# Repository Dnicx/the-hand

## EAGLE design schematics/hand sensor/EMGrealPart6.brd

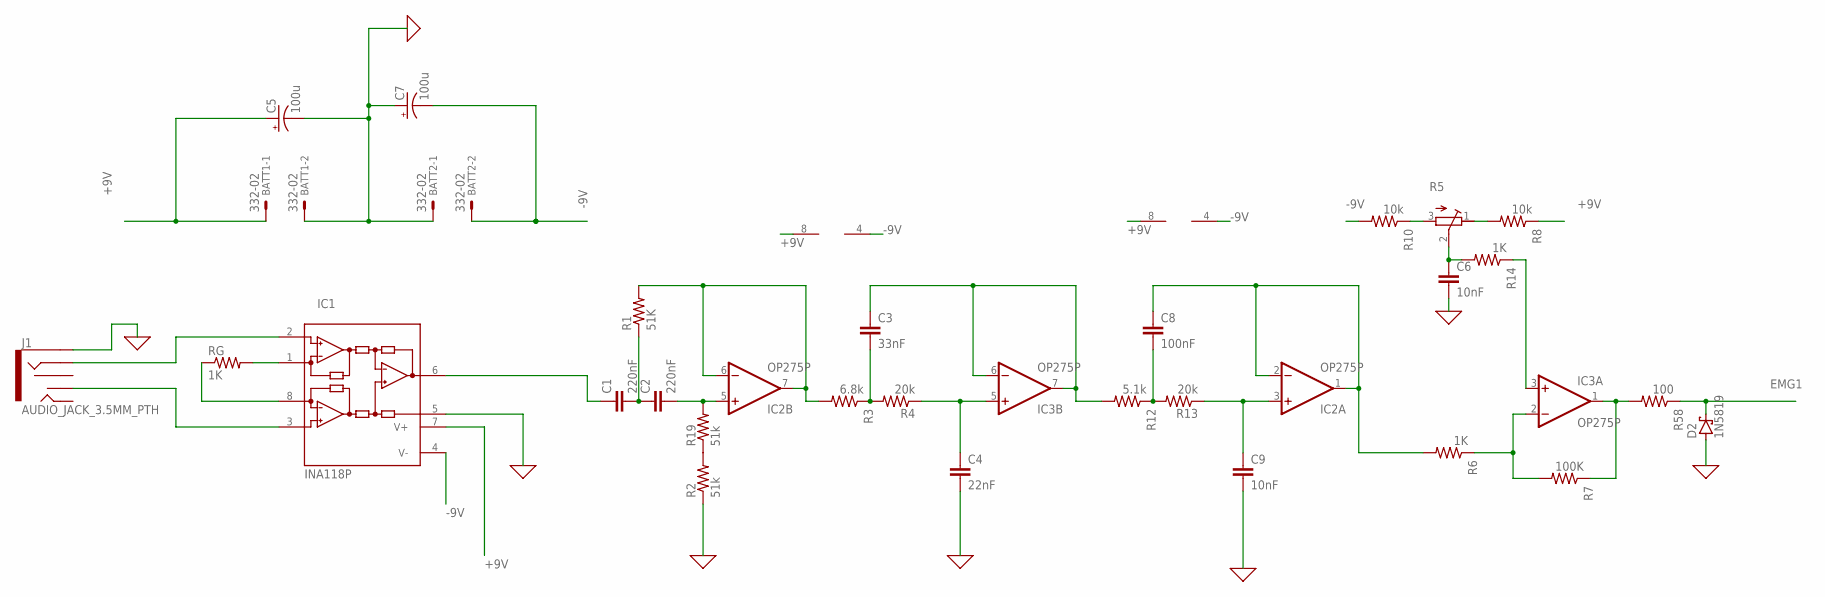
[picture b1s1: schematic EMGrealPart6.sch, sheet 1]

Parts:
BATT1, BATT2: 332-02
C1, C2: 220nF; C050-025X075
C3: 33nF; C050-025X075
C4: 22nF; C050-025X075
C5, C7: 100u; E2,5-6
C6, C9: 10nF; C050-025X075
C8: 100nF; C050-025X075
D2: 1N5819; F126Z12
IC1: INA118P; DIL08
IC2, IC3: OP275P; DIL08
J1: AUDIO_JACK_3.5MM_PTH; AUDIO-JACK
R1: 51K; 0207/12
R2, R19: 51k; 0207/12
R3: 6.8k; 0207/12
R4, R13: 20k; 0207/12
R5: R-TRIMMT93YA; RTRIMT93YA
R6, R14: 1K; 0207/12
R7: 100K; 0207/12
R8, R10: 10k; 0207/12
R12: 5.1k; 0207/12
R58: 100; 0207/12
RG: 1K; 0207/12

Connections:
0: BATT1.2, BATT2.1, C4.2, C5.-, C6.2, C7.+, C9.2, D2.A, IC1.5 (REF), J1.SLEEVE, R2.1; also elsewhere on the board
+9V: BATT1.1, C5.+, IC1.7 (V+), IC2.8 (V+), IC3.8 (V+), R8.1; also elsewhere on the board
-9V: BATT2.2, C7.-, IC1.4 (V-), IC2.4 (V-), IC3.4 (V-), R10.2; also elsewhere on the board
EMG1: D2.C, R58.1; also elsewhere on the board
unnamed: IC1.1 (RG), RG.2
unnamed: IC1.8 (RG), RG.1
unnamed: IC1.2 (-IN), J1.RING
unnamed: C8.2, R12.1, R13.2
unnamed: C1.2, C2.1, R1.1
unnamed: C1.1, IC1.6 (OUT)
unnamed: C2.2, IC2.5 (+IN), R19.2
unnamed: IC2.6 (-IN), IC2.7 (OUT), R1.2, R3.2
unnamed: C3.2, R3.1, R4.2
unnamed: C4.1, IC3.5 (+IN), R4.1
unnamed: C3.1, IC3.6 (-IN), IC3.7 (OUT), R12.2
unnamed: C9.1, IC2.3 (+IN), R13.1
unnamed: R5.3 (A), R10.1
unnamed: C6.1, R5.2 (S), R14.2
unnamed: IC3.2 (-IN), R6.1, R7.2
unnamed: R2.2, R19.1
unnamed: C8.1, IC2.1 (OUT), IC2.2 (-IN), R6.2
unnamed: R5.1 (E), R8.2
unnamed: IC3.3 (+IN), R14.1
unnamed: IC1.3 (+IN), J1.TSH
unnamed: IC3.1 (OUT), R7.1, R58.2

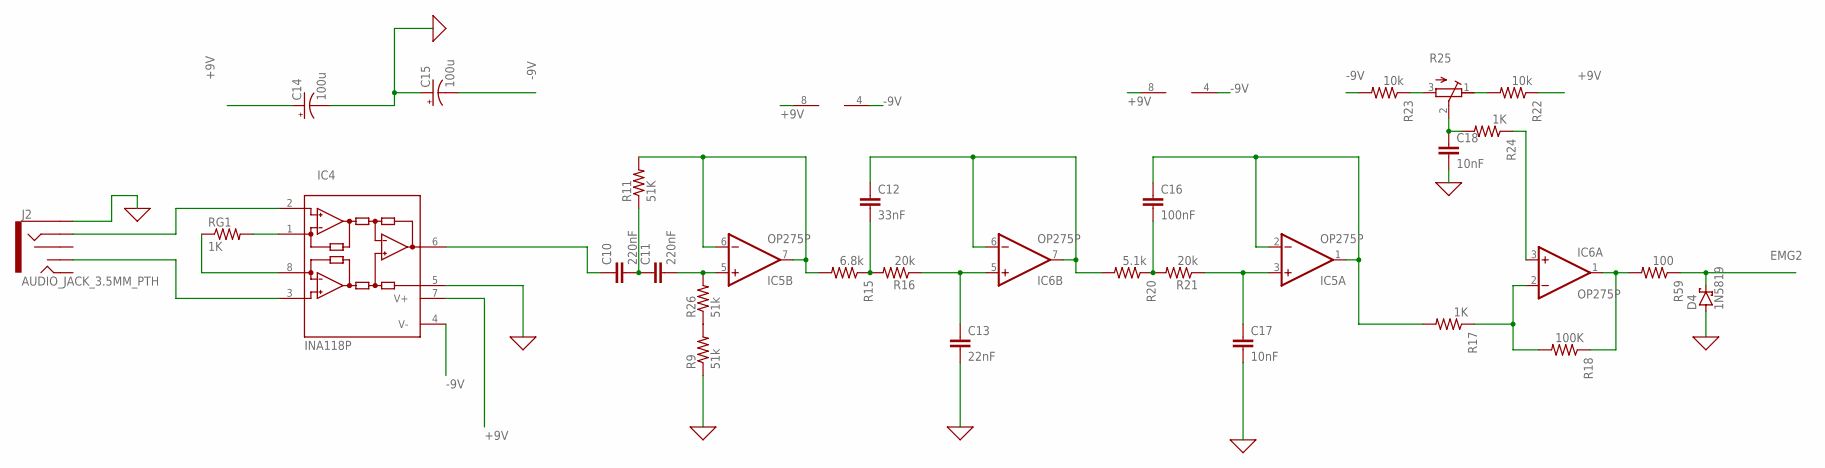
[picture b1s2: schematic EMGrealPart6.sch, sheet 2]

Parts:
C10, C11: 220nF; C050-025X075
C12: 33nF; C050-025X075
C13: 22nF; C050-025X075
C14, C15: 100u; E2,5-6
C16: 100nF; C050-025X075
C17, C18: 10nF; C050-025X075
D4: 1N5819; F126Z12
IC4: INA118P; DIL08
IC5, IC6: OP275P; DIL08
J2: AUDIO_JACK_3.5MM_PTH; AUDIO-JACK
R9, R26: 51k; 0207/12
R11: 51K; 0207/12
R15: 6.8k; 0207/12
R16, R21: 20k; 0207/12
R17, R24: 1K; 0207/12
R18: 100K; 0207/12
R20: 5.1k; 0207/12
R22, R23: 10k; 0207/12
R25: R-TRIMMT93YA; RTRIMT93YA
R59: 100; 0207/12
RG1: 1K; 0207/12

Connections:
0: C13.2, C14.-, C15.+, C17.2, C18.2, D4.A, IC4.5 (REF), J2.SLEEVE, R9.1; also elsewhere on the board
+9V: C14.+, IC4.7 (V+), IC5.8 (V+), IC6.8 (V+), R22.1; also elsewhere on the board
-9V: C15.-, IC4.4 (V-), IC5.4 (V-), IC6.4 (V-), R23.2; also elsewhere on the board
EMG2: D4.C, R59.1; also elsewhere on the board
unnamed: IC4.1 (RG), RG1.2
unnamed: IC4.8 (RG), RG1.1
unnamed: C10.1, IC4.6 (OUT)
unnamed: C10.2, C11.1, R11.1
unnamed: C11.2, IC5.5 (+IN), R26.2
unnamed: IC5.6 (-IN), IC5.7 (OUT), R11.2, R15.2
unnamed: C12.2, R15.1, R16.2
unnamed: C13.1, IC6.5 (+IN), R16.1
unnamed: C12.1, IC6.6 (-IN), IC6.7 (OUT), R20.2
unnamed: IC6.2 (-IN), R17.1, R18.2
unnamed: IC6.1 (OUT), R18.1, R59.2
unnamed: C16.2, R20.1, R21.2
unnamed: C17.1, IC5.3 (+IN), R21.1
unnamed: IC4.2 (-IN), J2.RING
unnamed: C16.1, IC5.1 (OUT), IC5.2 (-IN), R17.2
unnamed: IC4.3 (+IN), J2.TSH
unnamed: R23.1, R25.3 (A)
unnamed: R22.2, R25.1 (E)
unnamed: IC6.3 (+IN), R24.1
unnamed: C18.1, R24.2, R25.2 (S)
unnamed: R9.2, R26.1

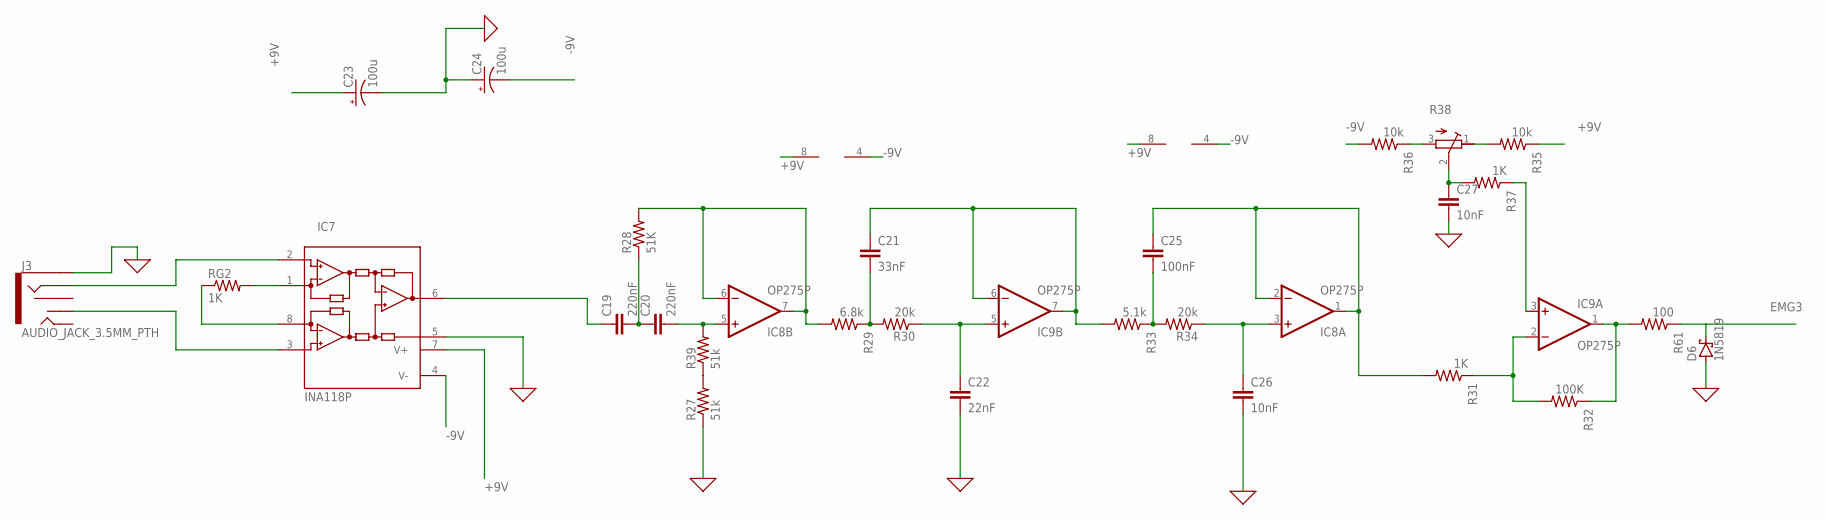
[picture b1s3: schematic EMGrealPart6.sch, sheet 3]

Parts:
C19, C20: 220nF; C050-025X075
C21: 33nF; C050-025X075
C22: 22nF; C050-025X075
C23, C24: 100u; E2,5-6
C25: 100nF; C050-025X075
C26, C27: 10nF; C050-025X075
D6: 1N5819; F126Z12
IC7: INA118P; DIL08
IC8, IC9: OP275P; DIL08
J3: AUDIO_JACK_3.5MM_PTH; AUDIO-JACK
R27, R39: 51k; 0207/12
R28: 51K; 0207/12
R29: 6.8k; 0207/12
R30, R34: 20k; 0207/12
R31, R37: 1K; 0207/12
R32: 100K; 0207/12
R33: 5.1k; 0207/12
R35, R36: 10k; 0207/12
R38: R-TRIMMT93YA; RTRIMT93YA
R61: 100; 0207/12
RG2: 1K; 0207/12

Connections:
0: C22.2, C23.-, C24.+, C26.2, C27.2, D6.A, IC7.5 (REF), J3.SLEEVE, R27.1; also elsewhere on the board
+9V: C23.+, IC7.7 (V+), IC8.8 (V+), IC9.8 (V+), R35.1; also elsewhere on the board
-9V: C24.-, IC7.4 (V-), IC8.4 (V-), IC9.4 (V-), R36.2; also elsewhere on the board
EMG3: D6.C, R61.1; also elsewhere on the board
unnamed: IC7.1 (RG), RG2.2
unnamed: IC7.8 (RG), RG2.1
unnamed: C19.1, IC7.6 (OUT)
unnamed: C19.2, C20.1, R28.1
unnamed: C20.2, IC8.5 (+IN), R39.2
unnamed: IC8.6 (-IN), IC8.7 (OUT), R28.2, R29.2
unnamed: C21.2, R29.1, R30.2
unnamed: C22.1, IC9.5 (+IN), R30.1
unnamed: C21.1, IC9.6 (-IN), IC9.7 (OUT), R33.2
unnamed: IC9.2 (-IN), R31.1, R32.2
unnamed: IC9.1 (OUT), R32.1, R61.2
unnamed: C25.2, R33.1, R34.2
unnamed: C26.1, IC8.3 (+IN), R34.1
unnamed: IC7.2 (-IN), J3.RING
unnamed: C25.1, IC8.1 (OUT), IC8.2 (-IN), R31.2
unnamed: IC7.3 (+IN), J3.TSH
unnamed: R36.1, R38.3 (A)
unnamed: R35.2, R38.1 (E)
unnamed: IC9.3 (+IN), R37.1
unnamed: C27.1, R37.2, R38.2 (S)
unnamed: R27.2, R39.1

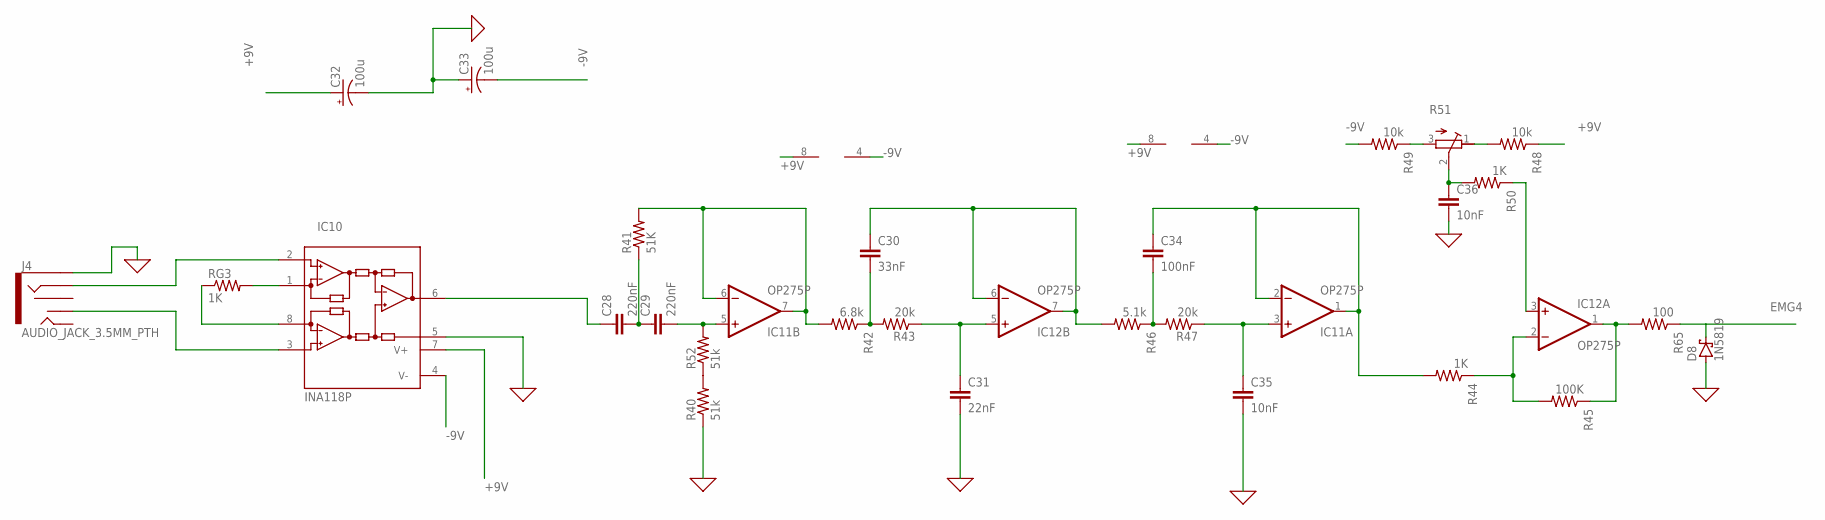
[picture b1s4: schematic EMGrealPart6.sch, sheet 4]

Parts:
C28, C29: 220nF; C050-025X075
C30: 33nF; C050-025X075
C31: 22nF; C050-025X075
C32, C33: 100u; E2,5-6
C34: 100nF; C050-025X075
C35, C36: 10nF; C050-025X075
D8: 1N5819; F126Z12
IC10: INA118P; DIL08
IC11, IC12: OP275P; DIL08
J4: AUDIO_JACK_3.5MM_PTH; AUDIO-JACK
R40, R52: 51k; 0207/12
R41: 51K; 0207/12
R42: 6.8k; 0207/12
R43, R47: 20k; 0207/12
R44, R50: 1K; 0207/12
R45: 100K; 0207/12
R46: 5.1k; 0207/12
R48, R49: 10k; 0207/12
R51: R-TRIMMT93YA; RTRIMT93YA
R65: 100; 0207/12
RG3: 1K; 0207/12

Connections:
0: C31.2, C32.-, C33.+, C35.2, C36.2, D8.A, IC10.5 (REF), J4.SLEEVE, R40.1; also elsewhere on the board
+9V: C32.+, IC10.7 (V+), IC11.8 (V+), IC12.8 (V+), R48.1; also elsewhere on the board
-9V: C33.-, IC10.4 (V-), IC11.4 (V-), IC12.4 (V-), R49.2; also elsewhere on the board
EMG4: D8.C; also elsewhere on the board
unnamed: IC10.1 (RG), RG3.2
unnamed: IC10.8 (RG), RG3.1
unnamed: C28.1, IC10.6 (OUT)
unnamed: C28.2, C29.1, R41.1
unnamed: C29.2, IC11.5 (+IN), R52.2
unnamed: IC11.6 (-IN), IC11.7 (OUT), R41.2, R42.2
unnamed: C30.2, R42.1, R43.2
unnamed: C31.1, IC12.5 (+IN), R43.1
unnamed: C30.1, IC12.6 (-IN), IC12.7 (OUT), R46.2
unnamed: IC12.2 (-IN), R44.1, R45.2
unnamed: IC12.1 (OUT), R45.1, R65.2
unnamed: C34.2, R46.1, R47.2
unnamed: C35.1, IC11.3 (+IN), R47.1
unnamed: IC10.2 (-IN), J4.RING
unnamed: C34.1, IC11.1 (OUT), IC11.2 (-IN), R44.2
unnamed: IC10.3 (+IN), J4.TSH
unnamed: R49.1, R51.3 (A)
unnamed: R48.2, R51.1 (E)
unnamed: IC12.3 (+IN), R50.1
unnamed: C36.1, R50.2, R51.2 (S)
unnamed: R40.2, R52.1

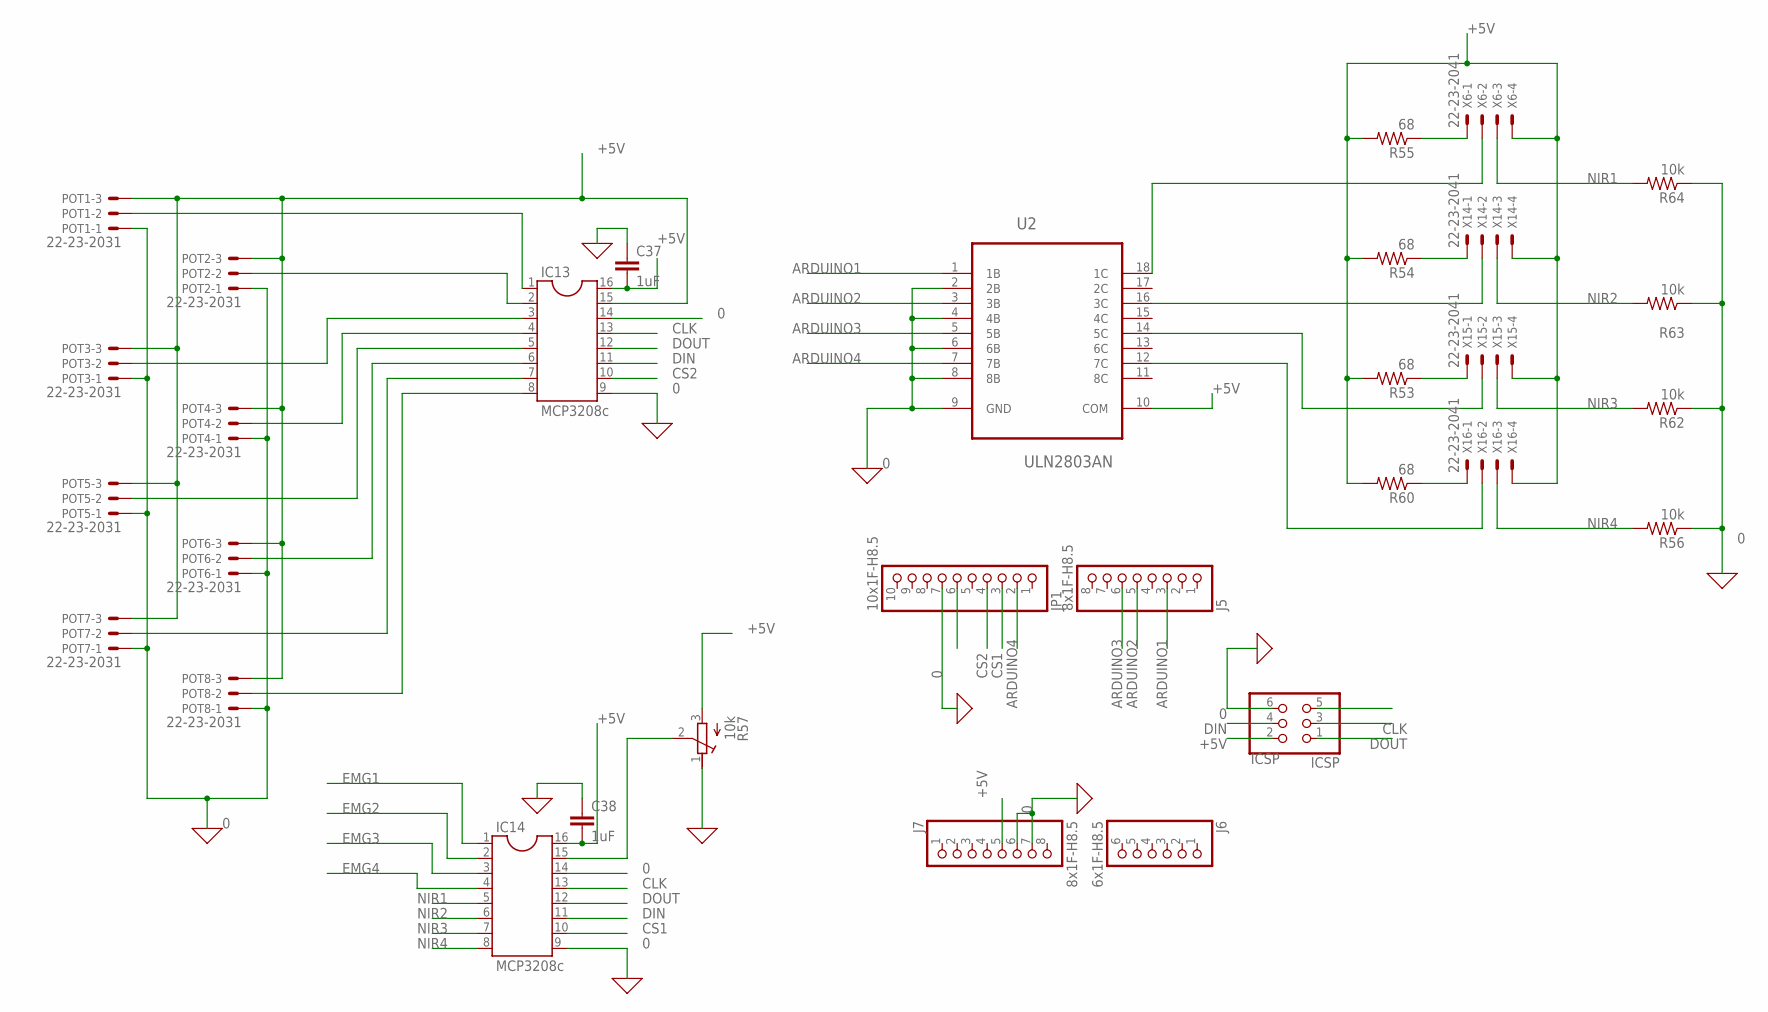
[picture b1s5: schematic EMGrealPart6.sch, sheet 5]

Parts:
C37, C38: 1uF; C050-025X075
IC13, IC14: MCP3208c; DIL16
ICSP: ICSP; 2X03
J5, J7: 8x1F-H8.5; 1X08
J6: 6x1F-H8.5; 1X06
JP1: 10x1F-H8.5; 1X10
POT1, POT2, POT3, POT4, POT5, POT6, POT7, POT8: 22-23-2031
R53, R54, R55, R60: 68; 0207/12
R56, R62, R63, R64: 10k; 0207/12
R57: 10k; RTRIMT93YA
U2: ULN2803AN; DIP254P762X393-18
X6, X14, X15, X16: 22-23-2041

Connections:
0: C37.1, C38.1, IC13.9, IC13.14, IC14.9, IC14.14, ICSP.6, J7.6, J7.7, JP1.7, POT1.1, POT2.1, POT3.1, POT4.1, POT5.1, POT6.1, POT7.1, POT8.1, R56.1, R57.1 (E), R62.1, R63.1, R64.1, U2.2 (2B), U2.4 (4B), U2.6 (6B), U2.8 (8B), U2.9 (GND); also elsewhere on the board
+5V: C37.2, C38.2, IC13.15, IC13.16, IC14.16, ICSP.2, J7.5, POT1.3, POT2.3, POT3.3, POT4.3, POT5.3, POT6.3, POT7.3, POT8.3, R53.2, R54.2, R55.2, R57.3 (A), R60.2, U2.10 (COM), X6.4, X14.4, X15.4, X16.4
ARDUINO1: J5.3, U2.1 (1B)
ARDUINO2: J5.5, U2.3 (3B)
ARDUINO3: J5.6, U2.5 (5B)
ARDUINO4: JP1.2, U2.7 (7B)
CLK: IC13.13, IC14.13, ICSP.3
CS1: IC14.10, JP1.3
CS2: IC13.10, JP1.4
DIN: IC13.11, IC14.11, ICSP.4
DOUT: IC13.12, IC14.12, ICSP.1
EMG1: IC14.1; also elsewhere on the board
EMG2: IC14.2; also elsewhere on the board
EMG3: IC14.3; also elsewhere on the board
EMG4: IC14.4; also elsewhere on the board
unnamed: U2.18 (1C), X6.2
unnamed: U2.16 (3C), X14.2
unnamed: U2.14 (5C), X15.2
unnamed: U2.12 (7C), X16.2
unnamed: IC13.1, POT1.2
unnamed: IC13.2, POT2.2
unnamed: IC13.3, POT3.2
unnamed: IC13.4, POT4.2
unnamed: IC13.5, POT5.2
unnamed: IC13.6, POT6.2
unnamed: IC13.7, POT7.2
unnamed: IC13.8, POT8.2
unnamed: IC14.15, R57.2 (S)
unnamed: R55.1, X6.1
unnamed: R54.1, X14.1
unnamed: R53.1, X15.1
unnamed: R60.1, X16.1
NIR1: IC14.5, R64.2, X6.3
NIR2: IC14.6, R63.2, X14.3
NIR3: IC14.7, R62.2, X15.3
NIR4: IC14.8, R56.2, X16.3

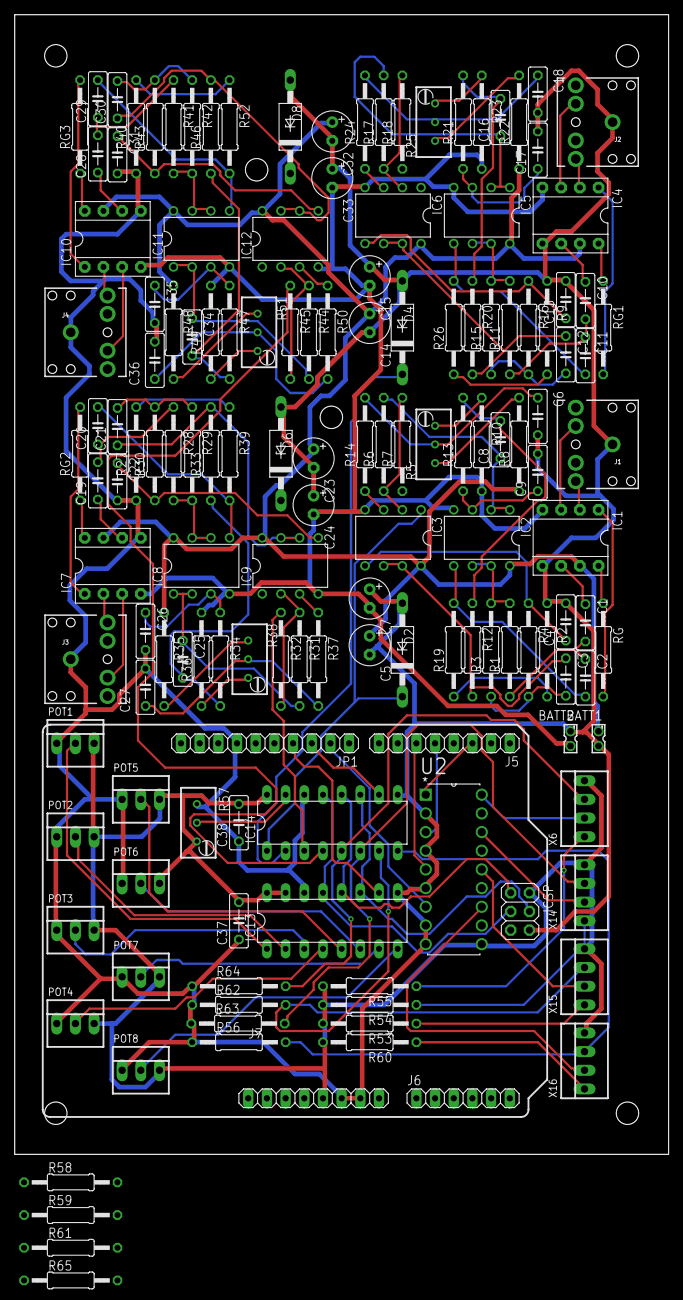
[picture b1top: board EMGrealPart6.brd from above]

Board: 2 copper layers, 88.9 x 154.9 mm, 149 parts (0 on the bottom side), 122 nets.

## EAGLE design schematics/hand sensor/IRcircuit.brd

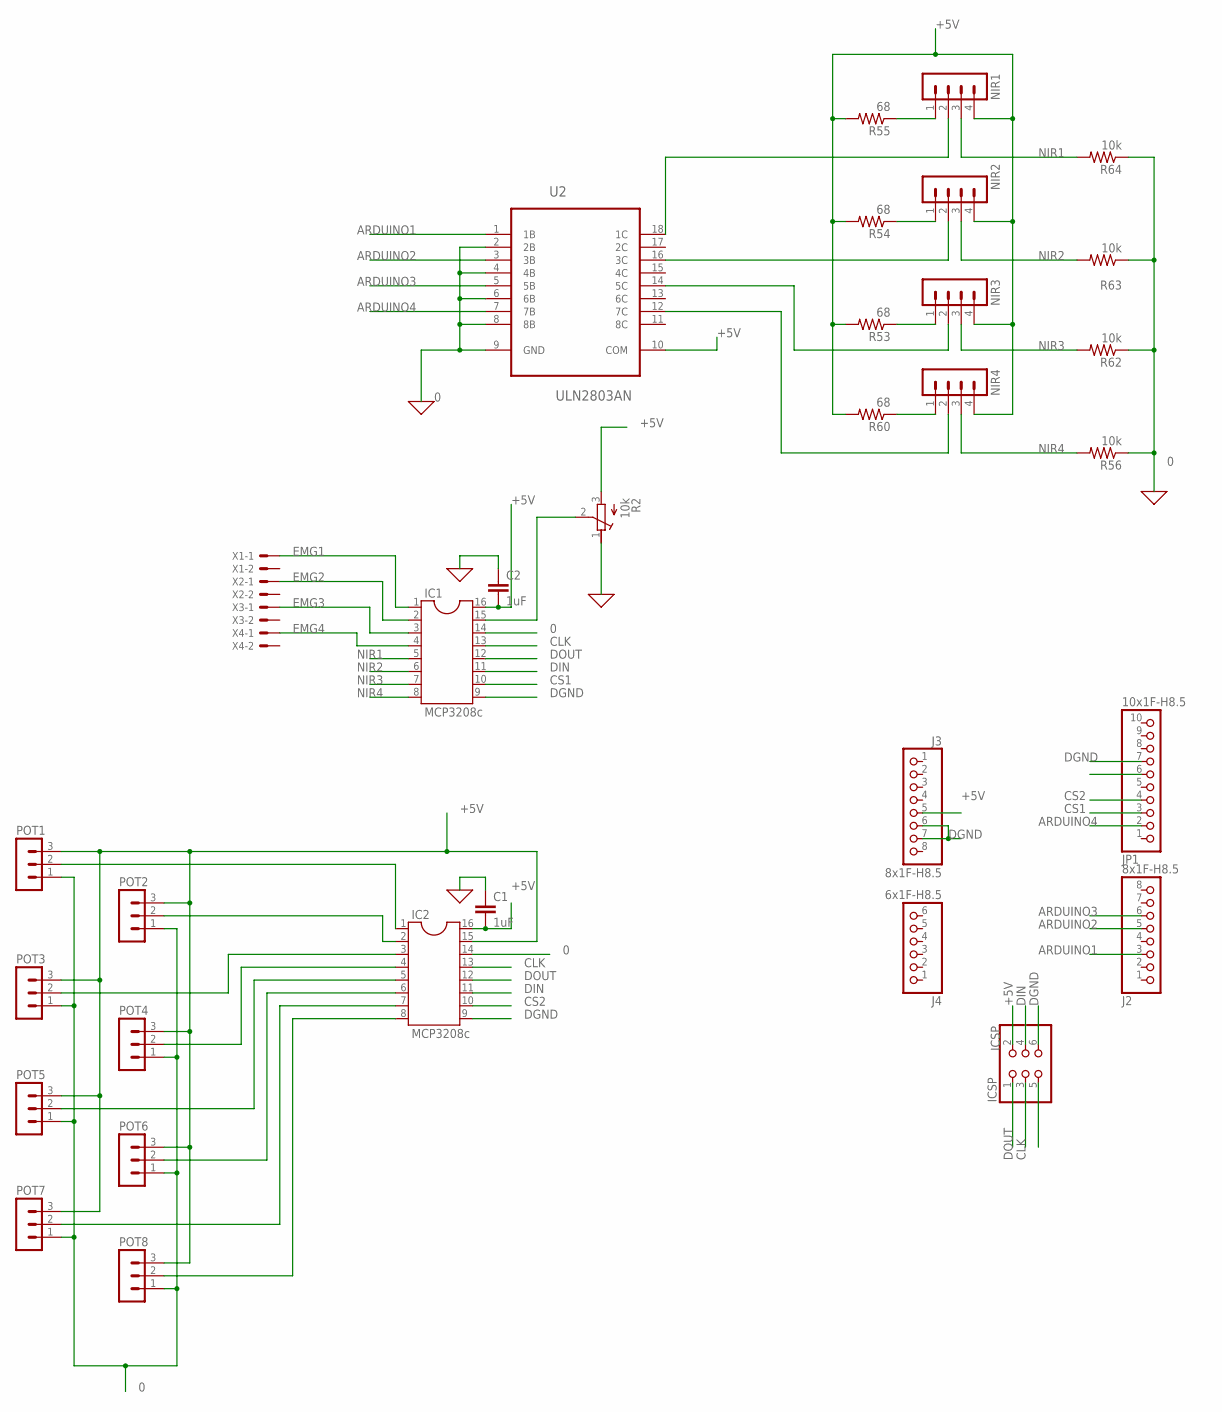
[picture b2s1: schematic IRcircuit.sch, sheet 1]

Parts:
C1, C2: 1uF; C050-025X075
IC1, IC2: MCP3208c; DIL16
ICSP: ICSP; 2X03
J2, J3: 8x1F-H8.5; 1X08
J4: 6x1F-H8.5; 1X06
JP1: 10x1F-H8.5; 1X10
NIR1, NIR2, NIR3, NIR4: MA04-1
POT1, POT2, POT3, POT4, POT5, POT6, POT7, POT8: MA03-1
R2: 10k; RTRIMT93YA
R53, R54, R55, R60: 68; 0207/12
R56, R62, R63, R64: 10k; 0207/12
U2: ULN2803AN; DIP254P762X393-18
X1, X2, X3, X4: 332-02

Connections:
0: C1.1, C2.1, IC1.14, IC2.14, POT1.1, POT2.1, POT3.1, POT4.1, POT5.1, POT6.1, POT7.1, POT8.1, R2.1 (E), R56.1, R62.1, R63.1, R64.1, U2.2 (2B), U2.4 (4B), U2.6 (6B), U2.8 (8B), U2.9 (GND)
+5V: C1.2, C2.2, IC1.16, IC2.15, IC2.16, ICSP.2, J3.5, NIR1.4, NIR2.4, NIR3.4, NIR4.4, POT1.3, POT2.3, POT3.3, POT4.3, POT5.3, POT6.3, POT7.3, POT8.3, R2.3 (A), R53.2, R54.2, R55.2, R60.2, U2.10 (COM)
ARDUINO1: J2.3, U2.1 (1B)
ARDUINO2: J2.5, U2.3 (3B)
ARDUINO3: J2.6, U2.5 (5B)
ARDUINO4: JP1.2, U2.7 (7B)
CLK: IC1.13, IC2.13, ICSP.3
CS1: IC1.10, JP1.3
CS2: IC2.10, JP1.4
DGND: IC1.9, IC2.9, ICSP.6, J3.6, J3.7, JP1.7
DIN: IC1.11, IC2.11, ICSP.4
DOUT: IC1.12, IC2.12, ICSP.1
EMG1: IC1.1, X1.1
EMG2: IC1.2, X2.1
EMG3: IC1.3, X3.1
EMG4: IC1.4, X4.1
unnamed: IC2.6, POT6.2
unnamed: IC2.1, POT1.2
unnamed: IC2.2, POT2.2
unnamed: IC2.3, POT3.2
unnamed: IC2.4, POT4.2
unnamed: IC2.5, POT5.2
unnamed: IC2.7, POT7.2
unnamed: IC2.8, POT8.2
unnamed: IC1.15, R2.2 (S)
unnamed: NIR1.2, U2.18 (1C)
unnamed: NIR2.2, U2.16 (3C)
unnamed: NIR3.2, U2.14 (5C)
unnamed: NIR4.2, U2.12 (7C)
unnamed: NIR1.1, R55.1
unnamed: NIR2.1, R54.1
unnamed: NIR3.1, R53.1
unnamed: NIR4.1, R60.1
NIR1: IC1.5, NIR1.3, R64.2
NIR2: IC1.6, NIR2.3, R63.2
NIR3: IC1.7, NIR3.3, R62.2
NIR4: IC1.8, NIR4.3, R56.2

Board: 2 copper layers, 35 parts (0 on the bottom side), 37 nets, no tracks yet.

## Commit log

2019-01-16 init git
2019-01-18 interrupt 1k Hz
2019-01-20 communicate all 8 channel
2019-03-28 update schematic
2019-05-10 implement NN, dummy data, 3d hand
2019-05-19 Implement socket transfering
    Implement socket transfering between Python and Unity.
    Arduino now has IR sensor implemented.
    Record 10 signal from sensor (before fix).
    Implement and train several models.
    Implement data analytic module.

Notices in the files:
parts and their libraries:
SparkFun-Connectors: Licensing: Creative Commons ShareAlike 4.0 International - https://creativecommons.org/licenses/by-sa/4.0
